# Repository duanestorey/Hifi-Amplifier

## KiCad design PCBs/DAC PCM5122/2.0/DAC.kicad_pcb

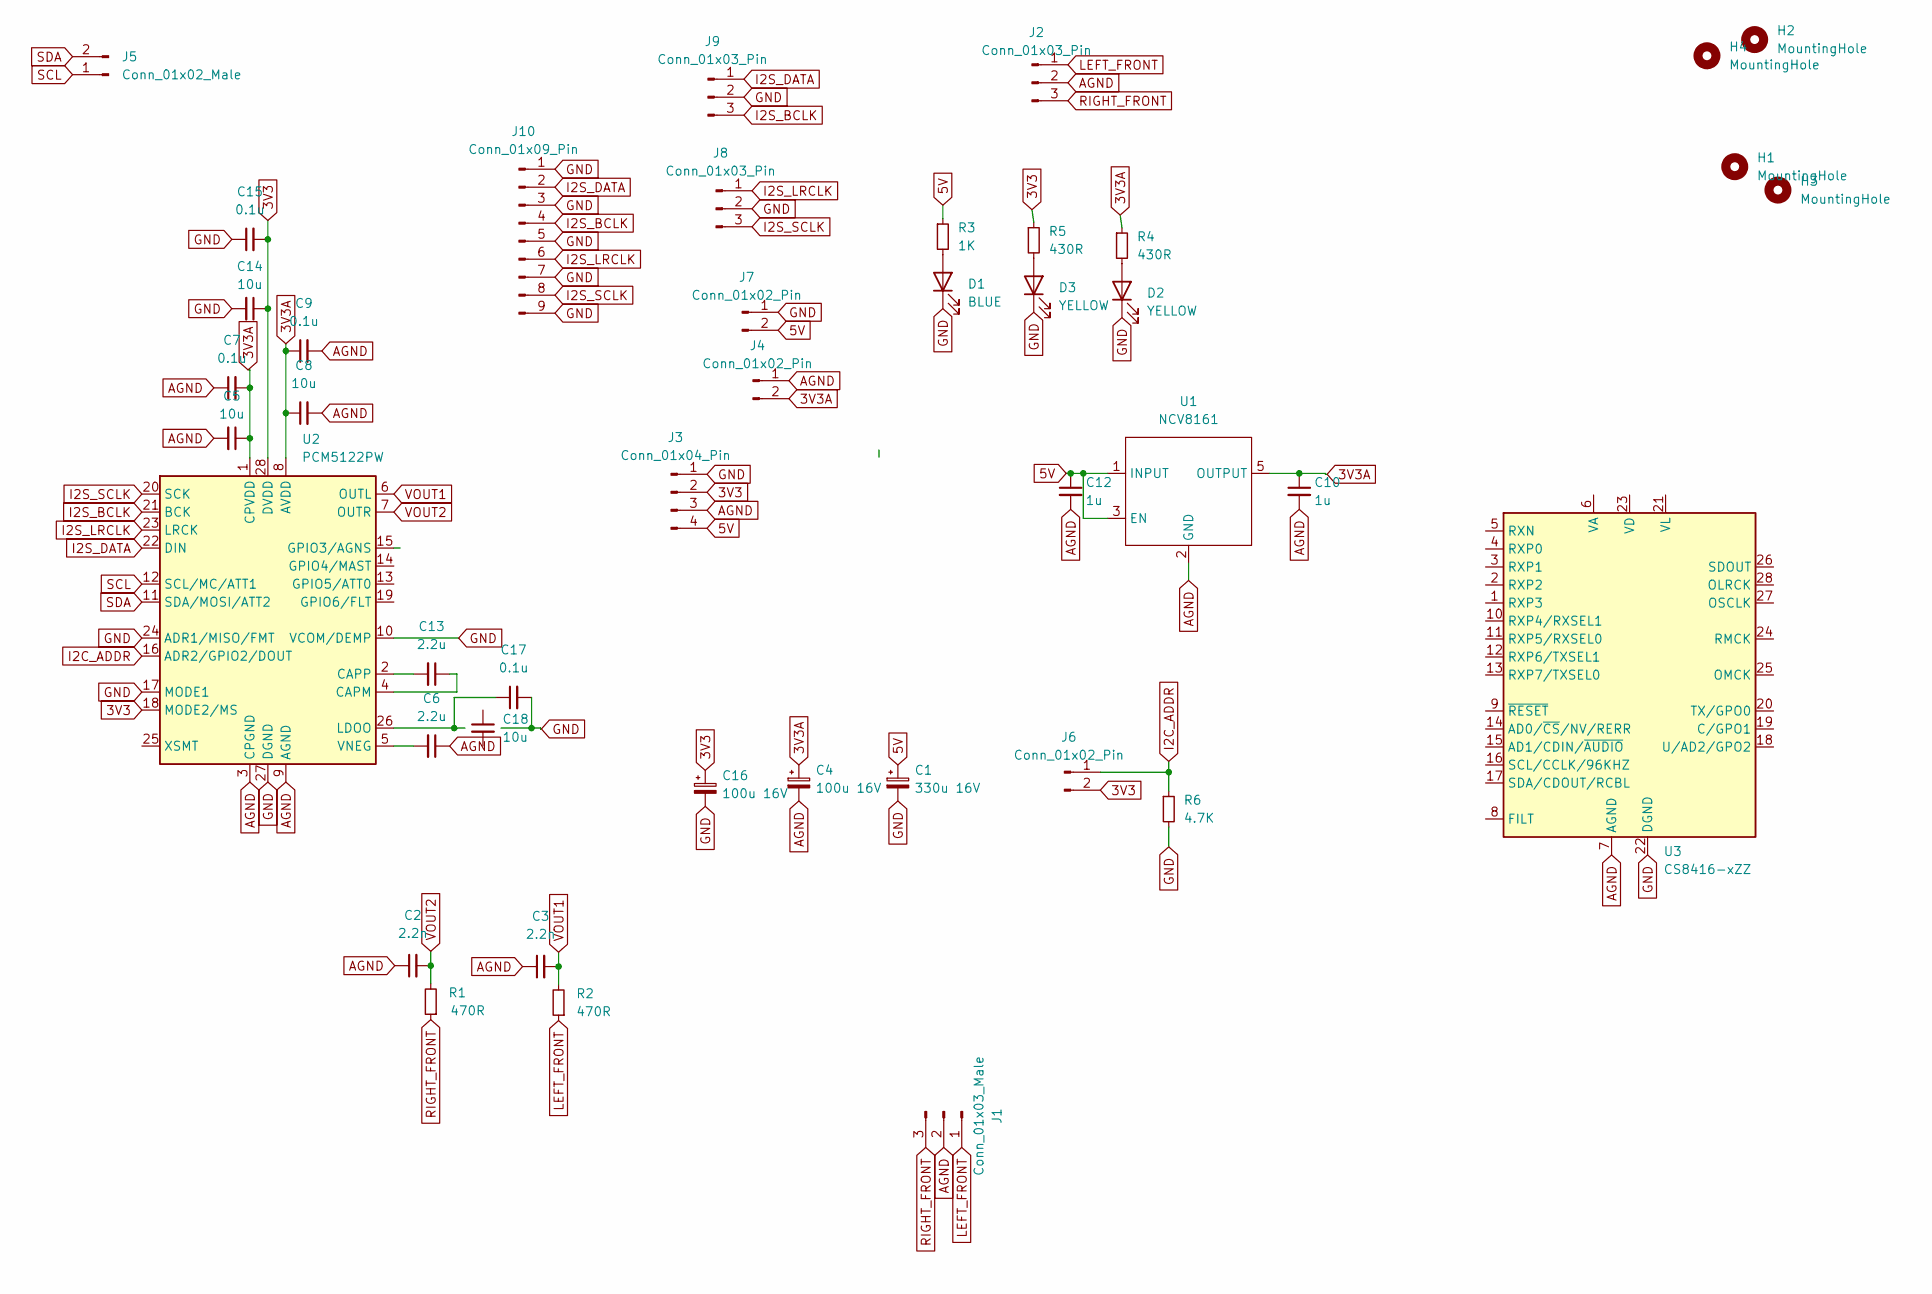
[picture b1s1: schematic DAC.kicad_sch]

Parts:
C1: 330u 16V; CP_Radial_D8.0mm_P2.50mm
C2, C3: 2.2n; C_1206_3216Metric_Pad1.33x1.80mm_HandSolder
C4, C16: 100u 16V; CP_Radial_D5.0mm_P2.50mm
C5, C8, C14, C18: 10u; C_1206_3216Metric_Pad1.33x1.80mm_HandSolder
C6, C13: 2.2u; C_1206_3216Metric_Pad1.33x1.80mm_HandSolder
C7, C9, C15, C17: 0.1u; C_0805_2012Metric_Pad1.18x1.45mm_HandSolder
C10, C12: 1u; C_1206_3216Metric_Pad1.33x1.80mm_HandSolder
D1: BLUE; LED_0805_2012Metric_Pad1.15x1.40mm_HandSolder
D2, D3: YELLOW; LED_0805_2012Metric_Pad1.15x1.40mm_HandSolder
H1, H2, H3, H4: MountingHole; MountingHole_3.2mm_M3
J1: Conn_01x03_Male; PinHeader_1x03_P2.54mm_Vertical
J2: Conn_01x03_Pin; JST_PH_B3B-PH-K_1x03_P2.00mm_Vertical
J3: Conn_01x04_Pin; JST_XH_B4B-XH-A_1x04_P2.50mm_Vertical
J4, J6, J7: Conn_01x02_Pin; PinHeader_1x02_P2.54mm_Vertical
J5: Conn_01x02_Male; JST_PH_B2B-PH-K_1x02_P2.00mm_Vertical
J8, J9: Conn_01x03_Pin; PinHeader_1x03_P2.54mm_Vertical
J10: Conn_01x09_Pin; PinSocket_1x09_P2.54mm_Vertical
R1, R2: 470R; R_1206_3216Metric_Pad1.30x1.75mm_HandSolder
R3: 1K; R_0603_1608Metric_Pad0.98x0.95mm_HandSolder
R4, R5: 430R; R_0603_1608Metric_Pad0.98x0.95mm_HandSolder
R6: 4.7K; R_0603_1608Metric_Pad0.98x0.95mm_HandSolder
U1: NCV8161; TSOT-23-5
U2: PCM5122PW; TSSOP-28_4.4x9.7mm_P0.65mm
U3: CS8416-xZZ; TSSOP-28-1EP_4.4x9.7mm_P0.65mm

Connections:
3V3: C14.1, C15.2, C16.1, J3.2, J6.2, R5.1, U2.18 (MODE2/MS), U2.28 (DVDD)
3V3A: C4.1, C5.1, C7.2, C8.1, C9.1, C10.1, J4.2, R4.1, U1.5 (OUTPUT), U2.1 (CPVDD), U2.8 (AVDD)
5V: C1.1, C12.1, J3.4, J7.2, R3.1, U1.1 (INPUT), U1.3 (EN)
AGND: C2.1, C3.1, C4.2, C5.2, C6.1, C7.1, C8.2, C9.2, C10.2, C12.2, J1.2, J2.2, J3.3, J4.1, U1.2 (GND), U2.3 (CPGND), U2.9 (AGND), U3.7 (AGND)
GND: C1.2, C14.2, C15.1, C16.2, C17.2, D1.1 (K), D2.1 (K), D3.1 (K), J3.1, J7.1, J8.2, J9.2, J10.1, J10.3, J10.5, J10.7, J10.9, R6.2, U2.10 (VCOM/DEMP), U2.17 (MODE1), U2.24 (ADR1/MISO/FMT), U2.27 (DGND), U3.22 (DGND)
I2C_ADDR: J6.1, R6.1, U2.16 (ADR2/GPIO2/DOUT)
I2S_BCLK: J9.3, J10.4, U2.21 (BCK)
I2S_DATA: J9.1, J10.2, U2.22 (DIN)
I2S_LRCLK: J8.1, J10.6, U2.23 (LRCK)
I2S_SCLK: J8.3, J10.8, U2.20 (SCK)
LEFT_FRONT: J1.1, J2.1, R2.1
unnamed: D1.2 (A), R3.2
unnamed: D2.2 (A), R4.2
unnamed: D3.2 (A), R5.2
unnamed: C13.1, U2.4 (CAPM)
unnamed: C13.2, U2.2 (CAPP)
unnamed: C17.1, U2.26 (LDOO)
unnamed: C6.2, U2.5 (VNEG)
RIGHT_FRONT: J1.3, J2.3, R1.1
SCL: J5.1, U2.12 (SCL/MC/ATT1)
SDA: J5.2, U2.11 (SDA/MOSI/ATT2)
VOUT1: C3.2, R2.2, U2.6 (OUTL)
VOUT2: C2.2, R1.2, U2.7 (OUTR)

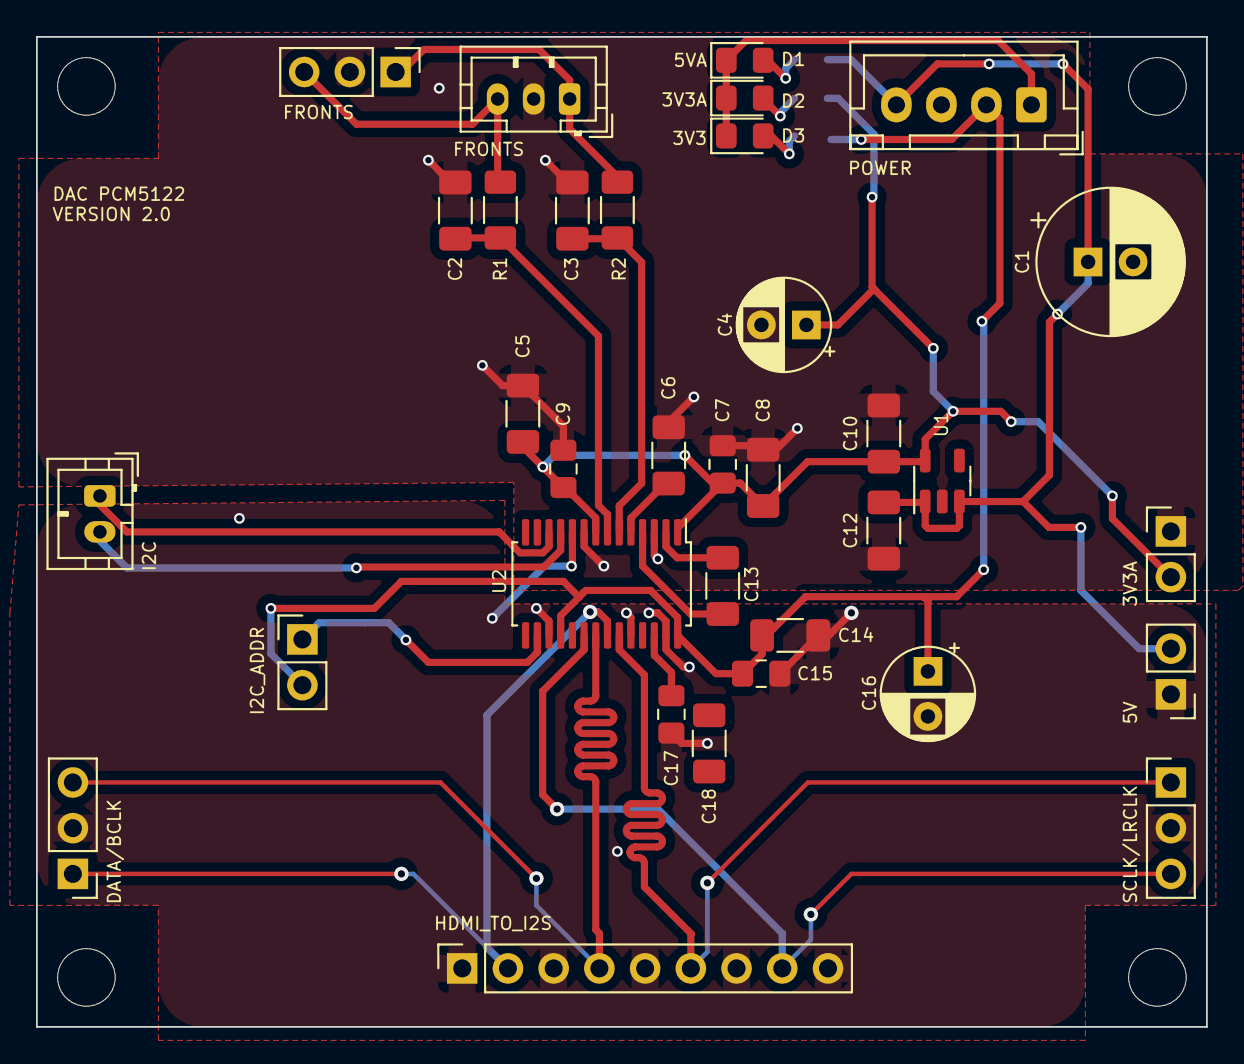
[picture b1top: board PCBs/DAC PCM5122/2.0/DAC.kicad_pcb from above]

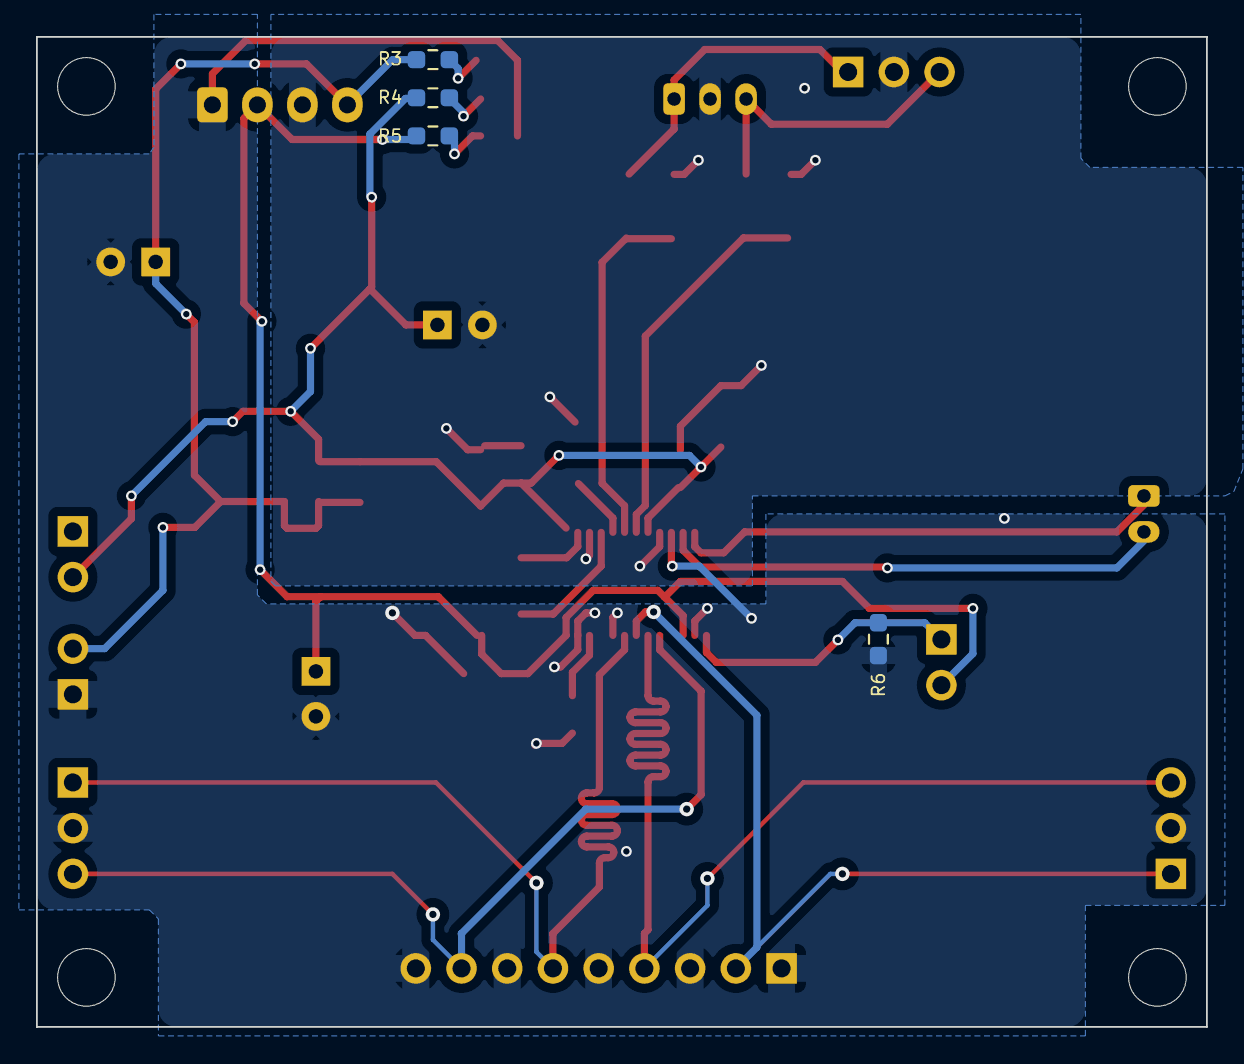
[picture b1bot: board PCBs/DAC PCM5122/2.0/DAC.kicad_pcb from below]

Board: 2 copper layers, 65.0 x 55.0 mm, 42 parts (4 on the bottom side), 23 nets.

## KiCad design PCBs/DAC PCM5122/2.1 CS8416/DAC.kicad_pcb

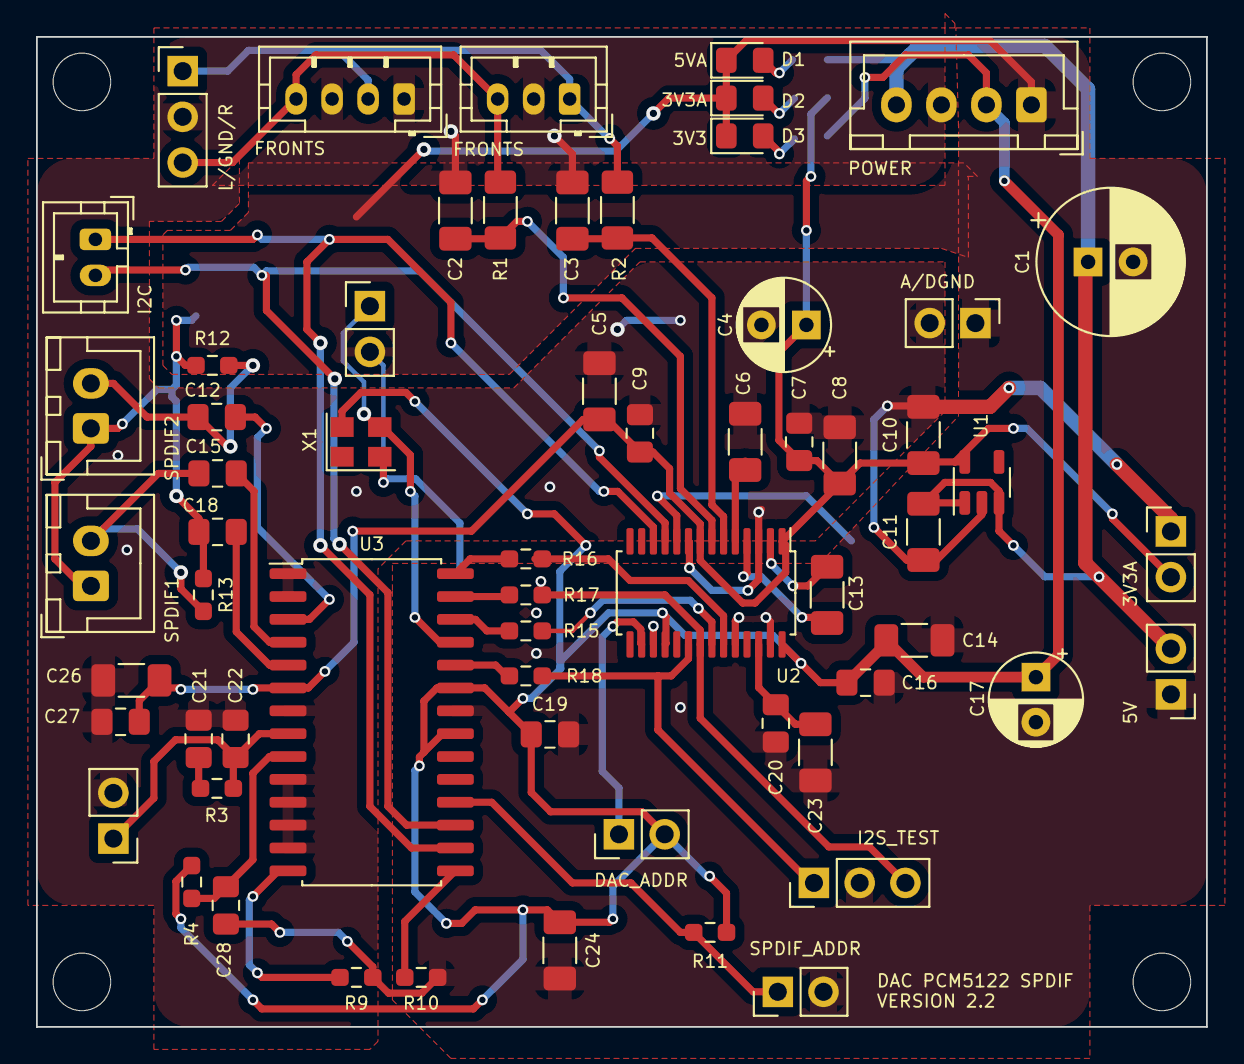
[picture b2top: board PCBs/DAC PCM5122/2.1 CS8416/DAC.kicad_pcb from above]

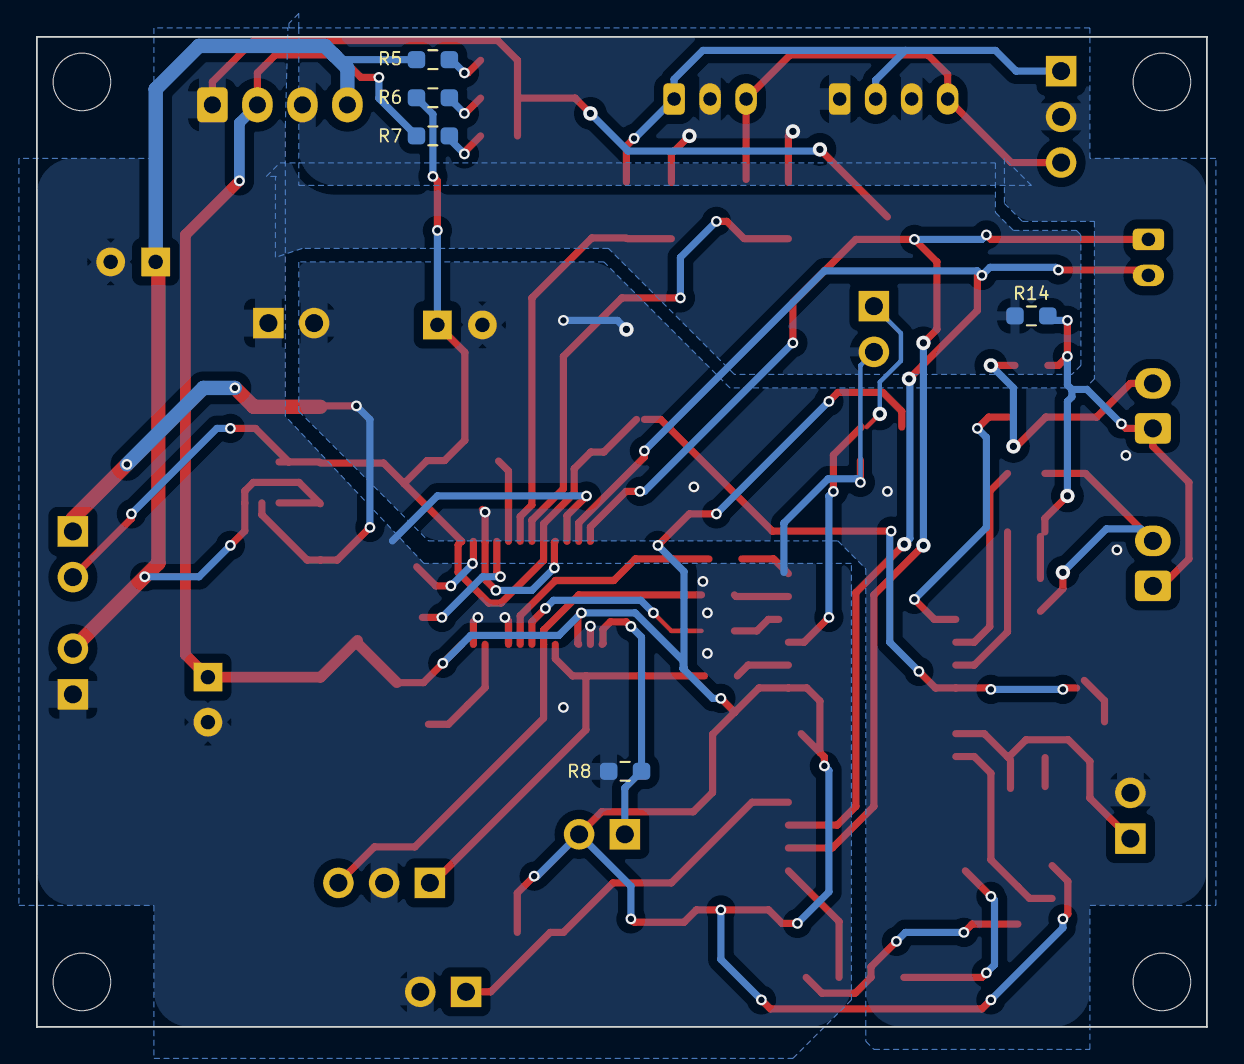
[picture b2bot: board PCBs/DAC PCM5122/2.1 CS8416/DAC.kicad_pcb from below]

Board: 2 copper layers, 65.0 x 55.0 mm, 71 parts (5 on the bottom side), 40 nets.

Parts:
C1: 330u 16V; CP_Radial_D8.0mm_P2.50mm
C2, C3: 2.2n; C_1206_3216Metric_Pad1.33x1.80mm_HandSolder
C4, C17: 100u 16V; CP_Radial_D5.0mm_P2.50mm
C5, C8, C14, C23, C24, C26: 10u; C_1206_3216Metric_Pad1.33x1.80mm_HandSolder
C6, C13: 2.2u; C_1206_3216Metric_Pad1.33x1.80mm_HandSolder
C7, C9, C16, C19, C20, C27: 0.1u; C_0805_2012Metric_Pad1.18x1.45mm_HandSolder
C10, C11: 1u; C_1206_3216Metric_Pad1.33x1.80mm_HandSolder
C12, C15, C18: 0.01u; C_0805_2012Metric_Pad1.18x1.45mm_HandSolder
C21: 22n; C_0805_2012Metric_Pad1.18x1.45mm_HandSolder
C22: 1n; C_0805_2012Metric_Pad1.18x1.45mm_HandSolder
C28: 1u; C_0805_2012Metric_Pad1.18x1.45mm_HandSolder
D1: BLUE; LED_0805_2012Metric_Pad1.15x1.40mm_HandSolder
D2, D3: YELLOW; LED_0805_2012Metric_Pad1.15x1.40mm_HandSolder
H1, H2, H3, H4: MountingHole; MountingHole_3.2mm_M3
J1: Conn_01x03_Male; PinHeader_1x03_P2.54mm_Vertical
J2: Conn_01x03_Pin; JST_PH_B3B-PH-K_1x03_P2.00mm_Vertical
J3: Conn_01x04_Pin; JST_XH_B4B-XH-A_1x04_P2.50mm_Vertical
J4: Conn_01x02_Male; JST_PH_B2B-PH-K_1x02_P2.00mm_Vertical
J5, J6, J8, J10, J11, J14, J15: Conn_01x02_Pin; PinHeader_1x02_P2.54mm_Vertical
J7, J9: Conn_01x02_Male; JST_XH_B2B-XH-A_1x02_P2.50mm_Vertical
J12: Conn_01x04_Pin; JST_PH_B4B-PH-K_1x04_P2.00mm_Vertical
J13: Conn_01x03_Pin; PinHeader_1x03_P2.54mm_Vertical
R1, R2: 470R; R_1206_3216Metric_Pad1.30x1.75mm_HandSolder
R3: 3K; R_0603_1608Metric_Pad0.98x0.95mm_HandSolder
R4: 100k; R_0603_1608Metric_Pad0.98x0.95mm_HandSolder
R5: 1K; R_0603_1608Metric_Pad0.98x0.95mm_HandSolder
R6, R7: 430R; R_0603_1608Metric_Pad0.98x0.95mm_HandSolder
R8, R9, R10, R11: 4.7K; R_0603_1608Metric_Pad0.98x0.95mm_HandSolder
R12, R13: 75R; R_0603_1608Metric_Pad0.98x0.95mm_HandSolder
R14: FERRITE; R_0603_1608Metric_Pad0.98x0.95mm_HandSolder
R15, R16, R17, R18: 22R; R_0603_1608Metric_Pad0.98x0.95mm_HandSolder
U1: NCV8161; TSOT-23-5
U2: PCM5122PW; TSSOP-28_4.4x9.7mm_P0.65mm
U3: CS8416-xZZ; SOIC-28W_7.5x17.9mm_P1.27mm
X1: ASE-xxxMHz; Oscillator_SMD_Abracon_ASE-4Pin_3.2x2.5mm

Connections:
3V3: C14.1, C16.2, C17.1, C19.1, C24.1, J3.2, J10.2, R4.2, R7.1, R11.1, U2.16 (ADR2/GPIO2/DOUT), U2.18 (MODE2/MS), U2.24 (ADR1/MISO/FMT), U2.28 (DVDD), U3.21 (VL), U3.23 (VD), X1.4 (Vdd)
3V3A: C4.1, C5.1, C7.2, C8.1, C9.1, C10.1, C26.2, C27.2, J6.2, R6.1, U1.5 (OUTPUT), U2.1 (CPVDD), U2.8 (AVDD), U3.6 (VA)
5V: C1.1, C11.1, J3.4, J8.2, R5.1, U1.1 (INPUT), U1.3 (EN)
AGND: C2.1, C3.1, C4.2, C5.2, C6.1, C7.1, C8.2, C9.2, C10.2, C11.2, C21.2, C22.1, C26.1, C27.1, J1.2, J2.2, J3.3, J5.2, J6.1, J12.1, J12.3, J15.2, U1.2 (GND), U2.3 (CPGND), U2.9 (AGND), U3.1 (RXP3), U3.2 (RXP2), U3.7 (AGND), U3.10 (RXP4/RXSEL1), U3.11 (RXP5/RXSEL0), U3.12 (RXP6/TXSEL1), U3.13 (RXP7/TXSEL0)
FGND: C18.1, J7.1, J9.1, R12.2, R13.2, R14.1
FILT: C22.2, J15.1, R3.2, U3.8 (FILT)
GND: C1.2, C14.2, C16.1, C17.2, C19.2, C20.2, C23.2, C24.2, C28.1, D1.1 (K), D2.1 (K), D3.1 (K), J3.1, J5.1, J8.1, J11.2, J13.2, J14.2, R8.2, R9.1, R10.1, R14.2, U2.10 (VCOM/DEMP), U2.17 (MODE1), U2.27 (DGND), U3.22 (DGND), X1.2 (GND)
I2C_ADDR: J10.1, R8.1
I2S_BCLK: J13.3, R17.2, U2.21 (BCK)
I2S_DATA: R15.2, U2.22 (DIN)
I2S_LRCLK: R16.2, U2.23 (LRCK)
I2S_SCLK: J13.1, R18.2, U2.20 (SCK)
LEFT_FRONT: J1.1, J2.1, J12.2, R2.1
unnamed: C21.1, R3.1
unnamed: D1.2 (A), R5.2
unnamed: D2.2 (A), R6.2
unnamed: D3.2 (A), R7.2
unnamed: J11.1, R11.2, U3.18 (U/AD2/GPO2)
unnamed: C13.1, U2.4 (CAPM)
unnamed: C13.2, U2.2 (CAPP)
unnamed: C20.1, C23.1, U2.26 (LDOO)
unnamed: C6.2, U2.5 (VNEG)
unnamed: R9.2, U3.14 (AD0/~CS/NV/RERR)
unnamed: R10.2, U3.15 (AD1/CDIN/~AUDIO)
unnamed: R16.1, U3.28 (OLRCK)
unnamed: R17.1, U3.27 (OSCLK)
unnamed: R18.1, U3.24 (RMCK)
unnamed: C18.2, U3.5 (RXN)
unnamed: C15.2, U3.4 (RXP0)
unnamed: C12.2, U3.3 (RXP1)
unnamed: R15.1, U3.26 (SDOUT)
unnamed: C28.2, R4.1, U3.9 (~RESET)
OMCK: J14.1, U3.25 (OMCK), X1.3 (OUT)
RIGHT_FRONT: J1.3, J2.3, J12.4, R1.1
SCL: J4.1, U2.12 (SCL/MC/ATT1), U3.16 (SCL/CCLK/96KHZ)
SDA: J4.2, U2.11 (SDA/MOSI/ATT2), U3.17 (SDA/CDOUT/RCBL)
SPDIF_P1: C15.1, J9.2, R13.1
SPDIF_P2: C12.1, J7.2, R12.1
VOUT1: C3.2, R2.2, U2.6 (OUTL)
VOUT2: C2.2, R1.2, U2.7 (OUTR)

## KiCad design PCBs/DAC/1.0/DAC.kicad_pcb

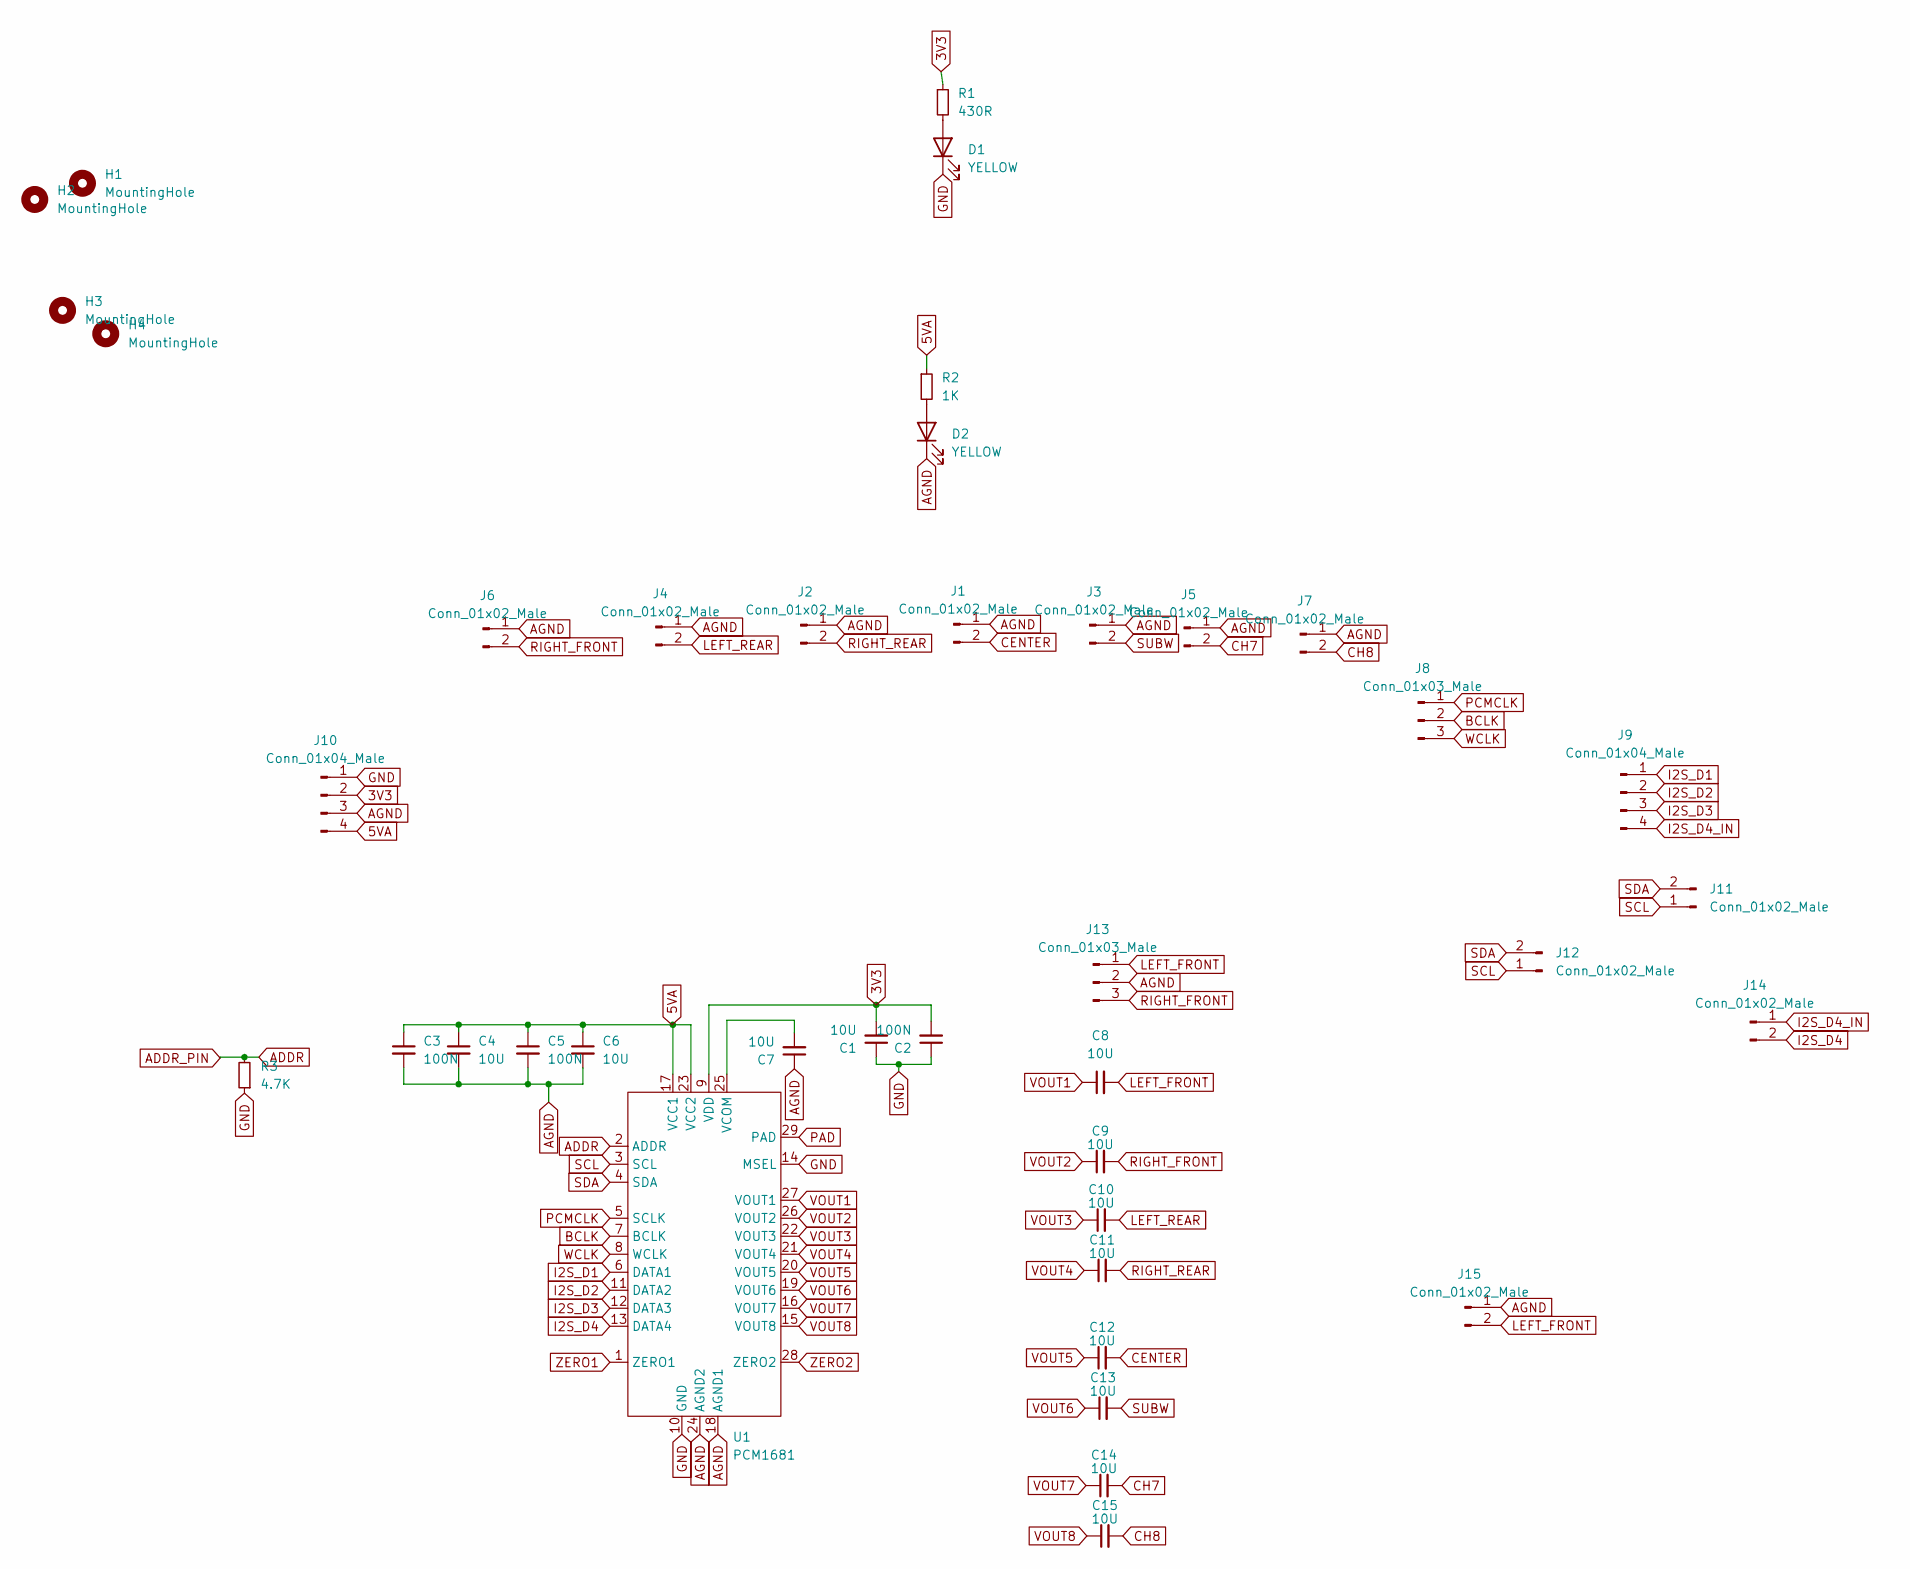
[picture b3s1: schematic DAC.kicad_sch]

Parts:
C1, C4, C6, C7: 10U; C_1206_3216Metric_Pad1.33x1.80mm_HandSolder
C2, C3, C5: 100N; C_0805_2012Metric_Pad1.18x1.45mm_HandSolder
C8, C9, C10, C11, C12, C13, C14, C15: 10U; CP_Radial_D5.0mm_P2.00mm
D1, D2: YELLOW; LED_0805_2012Metric_Pad1.15x1.40mm_HandSolder
H1, H2, H3, H4: MountingHole; MountingHole_3.2mm_M3
J1, J2, J3, J4, J5, J6, J7, J11, J12, J15: Conn_01x02_Male; JST_PH_B2B-PH-K_1x02_P2.00mm_Vertical
J8: Conn_01x03_Male; JST_PH_B3B-PH-K_1x03_P2.00mm_Vertical
J9, J10: Conn_01x04_Male; JST_PH_B4B-PH-K_1x04_P2.00mm_Vertical
J13: Conn_01x03_Male; PinHeader_1x03_P2.54mm_Vertical
J14: Conn_01x02_Male; PinHeader_1x02_P2.54mm_Vertical
R1: 430R; R_0603_1608Metric_Pad0.98x0.95mm_HandSolder
R2: 1K; R_0603_1608Metric_Pad0.98x0.95mm_HandSolder
R3: 4.7K; R_0603_1608Metric_Pad0.98x0.95mm_HandSolder
U1: PCM1681; HTSSOP-28-1EP_4.4x9.7mm_P0.65mm_EP3.4x9.5mm_Mask2.4x6.17mm_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

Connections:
3V3: C1.2, C2.2, J10.2, R1.1, U1.9 (VDD)
5VA: C3.1, C4.1, C5.1, C6.1, J10.4, R2.1, U1.17 (VCC1), U1.23 (VCC2)
ADDR: R3.2, U1.2 (ADDR)
AGND: C3.2, C4.2, C5.2, C6.2, C7.1, D2.1 (K), J1.1, J2.1, J3.1, J4.1, J5.1, J6.1, J7.1, J10.3, J13.2, J15.1, U1.18 (AGND1), U1.24 (AGND2)
BCLK: J8.2, U1.7 (BCLK)
CENTER: C12.2, J1.2
CH7: C14.2, J5.2
CH8: C15.2, J7.2
GND: C1.1, C2.1, D1.1 (K), J10.1, R3.1, U1.10 (GND), U1.14 (MSEL)
I2S_D1: J9.1, U1.6 (DATA1)
I2S_D2: J9.2, U1.11 (DATA2)
I2S_D3: J9.3, U1.12 (DATA3)
I2S_D4: J14.2, U1.13 (DATA4)
I2S_D4_IN: J9.4, J14.1
LEFT_FRONT: C8.2, J13.1, J15.2
LEFT_REAR: C10.2, J4.2
unnamed: D1.2 (A), R1.2
unnamed: D2.2 (A), R2.2
unnamed: C7.2, U1.25 (VCOM)
PAD: U1.29 (PAD)
PCMCLK: J8.1, U1.5 (SCLK)
RIGHT_FRONT: C9.2, J6.2, J13.3
RIGHT_REAR: C11.2, J2.2
SCL: J11.1, J12.1, U1.3 (SCL)
SDA: J11.2, J12.2, U1.4 (SDA)
SUBW: C13.2, J3.2
VOUT1: C8.1, U1.27 (VOUT1)
VOUT2: C9.1, U1.26 (VOUT2)
VOUT3: C10.1, U1.22 (VOUT3)
VOUT4: C11.1, U1.21 (VOUT4)
VOUT5: C12.1, U1.20 (VOUT5)
VOUT6: C13.1, U1.19 (VOUT6)
VOUT7: C14.1, U1.16 (VOUT7)
VOUT8: C15.1, U1.15 (VOUT8)
WCLK: J8.3, U1.8 (WCLK)
ZERO1: U1.1 (ZERO1)
ZERO2: U1.28 (ZERO2)

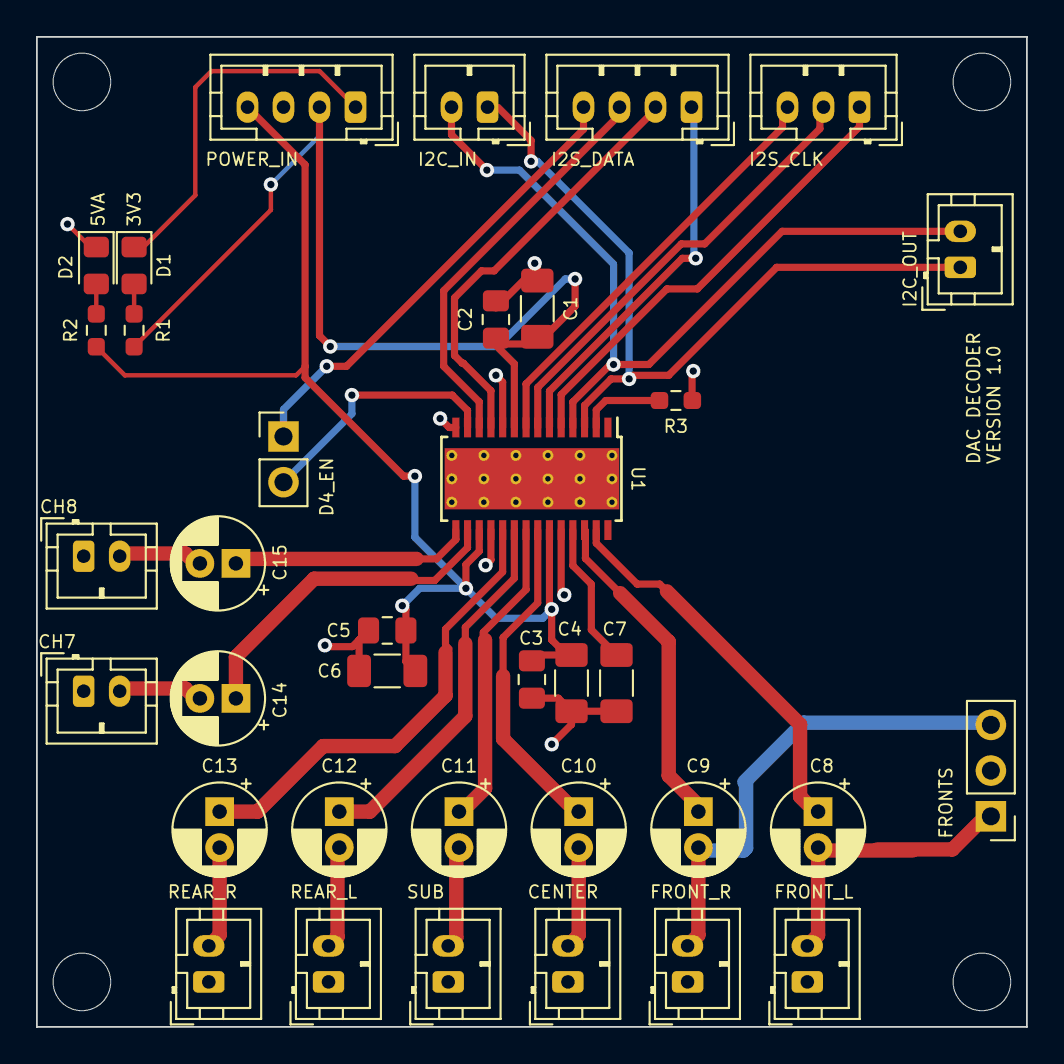
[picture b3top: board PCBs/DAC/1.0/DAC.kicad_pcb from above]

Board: 2 copper layers, 55.0 x 55.0 mm, 40 parts (0 on the bottom side), 34 nets.
